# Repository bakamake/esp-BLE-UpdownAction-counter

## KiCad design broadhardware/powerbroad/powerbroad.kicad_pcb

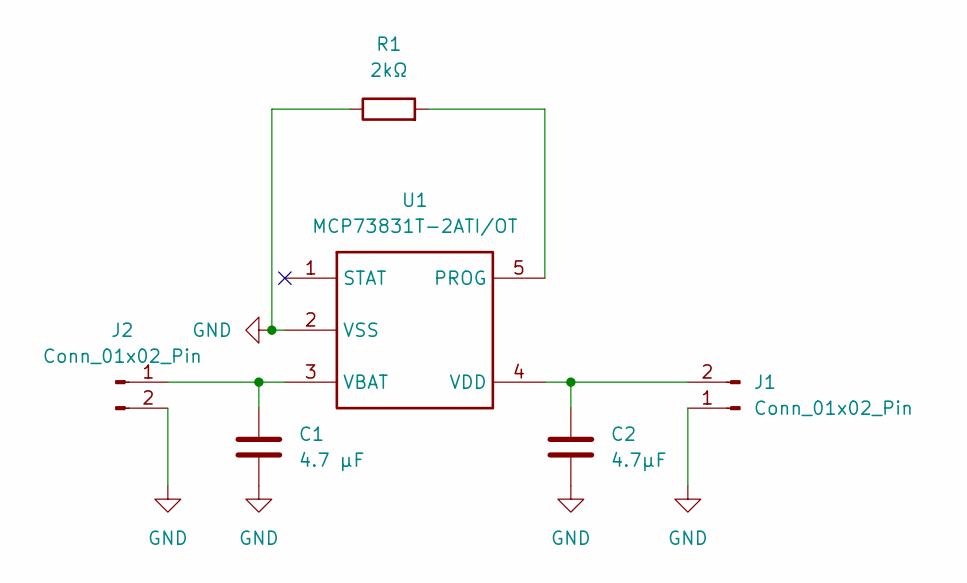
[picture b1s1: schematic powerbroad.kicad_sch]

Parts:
C1: 4.7 µF; C_0603_1608Metric
C2: 4.7μF; C_0603_1608Metric
J1, J2: Conn_01x02_Pin; JST_SH_BM02B-SRSS-TB_1x02-1MP_P1.00mm_Vertical
R1: 2kΩ; R_0603_1608Metric
U1: MCP73831T-2ATI/OT; SOT-23-5_L3.0-W1.7-P0.95-LS2.8-BR; LCSC Part C14879

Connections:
GND: C1.2, C2.2, J1.1, J2.2, R1.1, U1.2 (VSS)
unnamed: C2.1, J1.2, U1.4 (VDD)
unnamed: C1.1, J2.1, U1.3 (VBAT)
unnamed: R1.2, U1.5 (PROG)

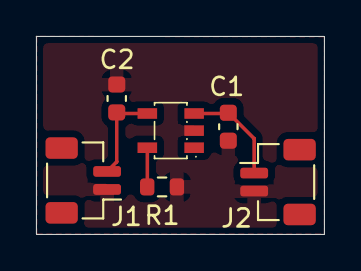
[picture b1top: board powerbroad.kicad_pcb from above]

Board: 2 copper layers, 16.0 x 11.0 mm, 6 parts (0 on the bottom side), 4 nets.

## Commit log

2026-04-07 Initial commit: ESP32 BLE Up/Down Action Counter
    - ESP-IDF project for BLE motion detection
    - LSM6DS3 IMU integration via I2C
    - Movement counter logic
    - KiCad hardware design for broadhardware
2026-04-24 锂电池电源板子
